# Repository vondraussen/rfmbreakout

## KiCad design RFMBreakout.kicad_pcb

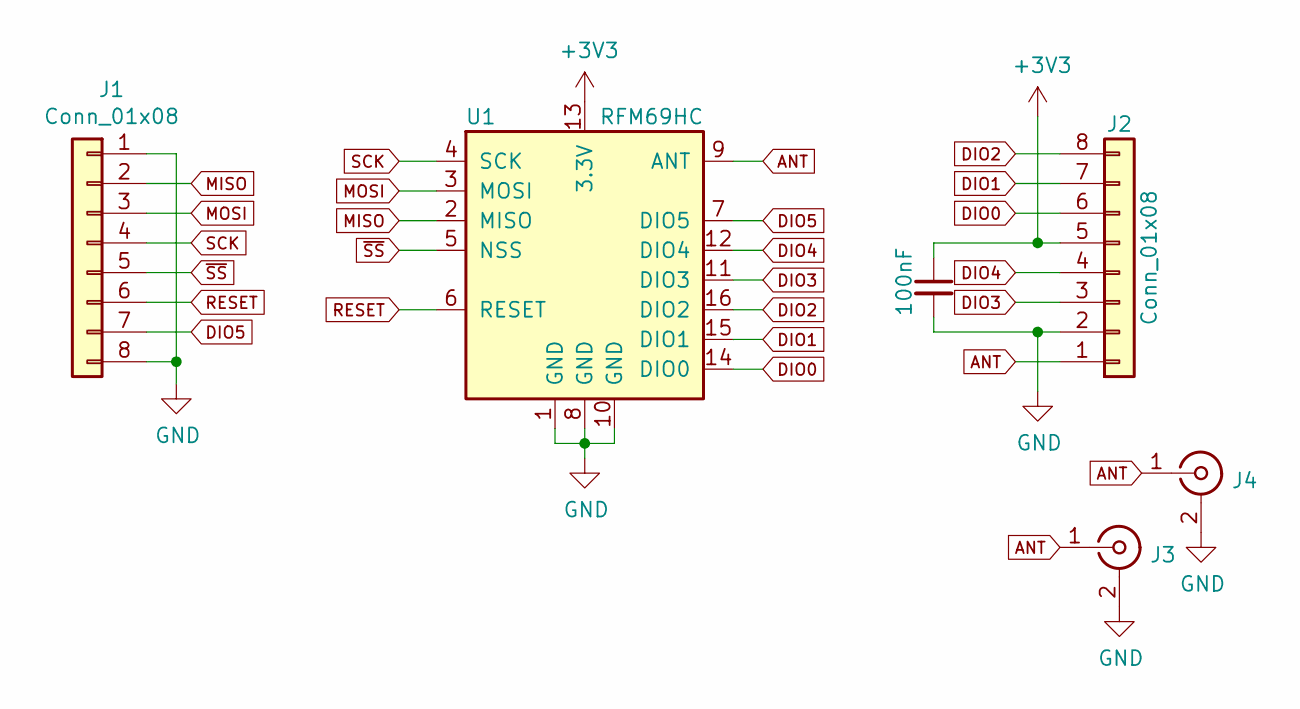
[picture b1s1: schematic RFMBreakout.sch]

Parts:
C1: 100nF; C_0805_2012Metric_Pad1.18x1.45mm_HandSolder
J1, J2: Conn_01x08; PinHeader_1x08_P2.54mm_Vertical
J3: Conn_Coaxial; U.FL_Molex_MCRF_73412-0110_Vertical
J4: Conn_Coaxial; SMA_Molex_73251-2200_Horizontal
U1: RFM69HC; HOPERF_RFM9XW_SMD

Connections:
+3V3: C1.1, J2.5, U1.13 (3.3V)
ANT: J2.1, J3.1 (In), J4.1 (In), U1.9 (ANT)
DIO0: J2.6, U1.14 (DIO0)
DIO1: J2.7, U1.15 (DIO1)
DIO2: J2.8, U1.16 (DIO2)
DIO3: J2.3, U1.11 (DIO3)
DIO4: J2.4, U1.12 (DIO4)
DIO5: J1.7, U1.7 (DIO5)
GND: C1.2, J1.1, J1.8, J2.2, J3.2 (Ext), J4.2 (Ext), U1.1 (GND), U1.8 (GND), U1.10 (GND)
MISO: J1.2, U1.2 (MISO)
MOSI: J1.3, U1.3 (MOSI)
RESET: J1.6, U1.6 (RESET)
SCK: J1.4, U1.4 (SCK)
~SS: J1.5, U1.5 (NSS)

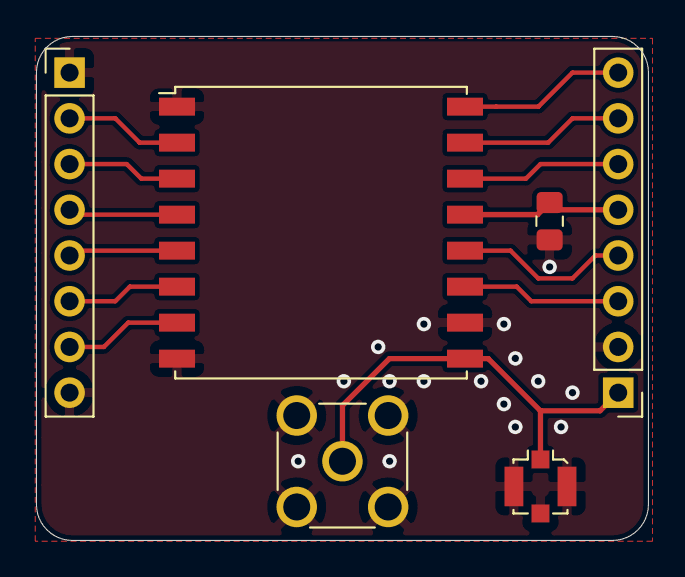
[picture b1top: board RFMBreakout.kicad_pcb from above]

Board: 2 copper layers, 34.0 x 28.0 mm, 6 parts (0 on the bottom side), 14 nets.

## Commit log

2021-12-05 init commit
